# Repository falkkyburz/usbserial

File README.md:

# USB to Serial Converter

This is a USB to serial (UART) converter employing the FTDI FT230XS chip designed in KiCad. I 
included an optional digital isolator for noisy environments or when galvanic 
isolation is required. 

## BOM

I also included the interactive html BOM (usbserial.html) 

| References     | Value                     | Footprint | Quantity |
|----------------|---------------------------|-----------|----------|
| C1, C2, C7, C8 | 100n                      | 0603      | 4        |
| C4, C5         | 47p                       | 0603      | 2        |
| C3             | 10n                       | 0603      | 1        |
| C6             | 4.7u                      | 0603      | 1        |
| R1, R2         | 270R                      | 0603      | 2        |
| R3, R4         | 27R                       | 0603      | 2        |
| D1, D2         | green                     | 0603      | 2        |
| U1             | Si8642BB-B-IS1            | SOIC-16   | 1        |
| U2             | FT230XS                   | SSOP-16   | 1        |
| FB1            | MI0603J601R-10            | 0603      | 1        |
| JP1 - JP6      | Jumper (if U1 not placed) | 1206      | 6        |
| J1             | Header 4pin, 2.54mm       | -         | 1        |
| J2             | USB-Micro WE 629105150521 | -         | 1        |

## Datasheets

* [Si8642BB-B-IS1](https://www.silabs.com/documents/public/data-sheets/si864x-datasheet.pdf)
* [FT230XS](https://www.ftdichip.com/Support/Documents/DataSheets/ICs/DS_FT230X.pdf)
* [MI0603J601R-10](https://www.laird.com/sites/default/files/2019-04/MI0603J601R-10_0.pdf)
* [WE 629105150521](https://www.we-online.com/catalog/en/COM_MICRO_SMT_TYPE_B_HORIZONTAL_HIGH_CURRENT/)

## Prototype

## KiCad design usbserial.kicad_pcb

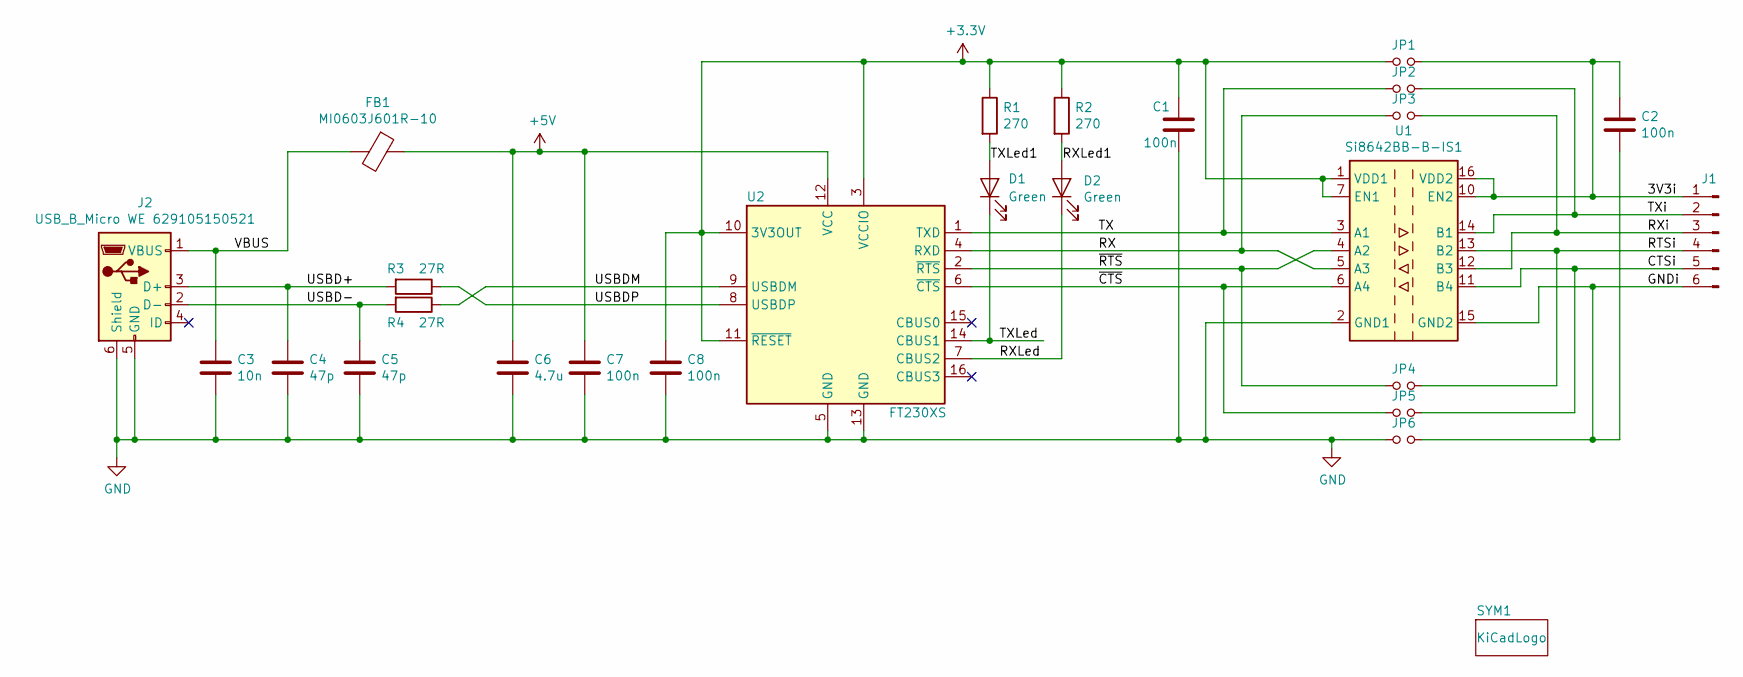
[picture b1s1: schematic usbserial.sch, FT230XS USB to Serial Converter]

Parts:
C1, C2, C7, C8: 100n; C_0603_1608Metric_Pad1.05x0.95mm_HandSolder
C3: 10n; C_0603_1608Metric_Pad1.05x0.95mm_HandSolder
C4, C5: 47p; C_0603_1608Metric_Pad1.05x0.95mm_HandSolder
C6: 4.7u; C_0603_1608Metric_Pad1.05x0.95mm_HandSolder
D1, D2: Green; LED_0603_1608Metric_Pad1.05x0.95mm_HandSolder
FB1: MI0603J601R-10; L_0603_1608Metric_Pad1.05x0.95mm_HandSolder
J1: Conn_01x06_Male; PinHeader_1x06_P2.54mm_Vertical
J2: USB_B_Micro WE 629105150521; USB_Micro-B_Wuerth_629105150521_CircularHoles
JP1, JP2, JP3, JP4, JP5, JP6: Jumper_NO_Small; R_1206_3216Metric_Pad1.42x1.75mm_HandSolder
R1, R2: 270; R_0603_1608Metric_Pad1.05x0.95mm_HandSolder
R3, R4: 27R; R_0603_1608Metric_Pad1.05x0.95mm_HandSolder
SYM1: KiCadLogo; KiCad-Logo2_5mm_SilkScreen
U1: Si8642BB-B-IS1; SOIC-16_3.9x9.9mm_P1.27mm
U2: FT230XS; SSOP-16_3.9x4.9mm_P0.635mm

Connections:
+3V3: C1.1, C8.1, JP1.1, R1.1, R2.1, U1.1 (VDD1), U1.7 (EN1), U2.3 (VCCIO), U2.10 (3V3OUT), U2.11 (~RESET)
+5V: C6.1, C7.1, FB1.1, U2.12 (VCC)
/3V3i: C2.1, J1.1, JP1.2, U1.10 (EN2), U1.16 (VDD2)
/CTSi: J1.5, JP5.2, U1.11 (B4)
/GNDi: C2.2, J1.6, JP6.2, U1.9 (GND2), U1.15 (GND2)
/RTSi: J1.4, JP4.2, U1.13 (B2)
/RX: JP3.1, U1.5 (A3), U2.4 (RXD)
/RXLed: D2.1 (K), U2.7 (CBUS2)
/RXLed1: D2.2 (A), R2.2
/RXi: J1.3, JP3.2, U1.12 (B3)
/TX: JP2.1, U1.3 (A1), U2.1 (TXD)
/TXLed: D1.1 (K), U2.14 (CBUS1)
/TXLed1: D1.2 (A), R1.2
/TXi: J1.2, JP2.2, U1.14 (B1)
/USBD+: C4.1, J2.3 (D+), R3.2
/USBD-: C5.1, J2.2 (D-), R4.2
/USBDM: R4.1, U2.9 (USBDM)
/USBDP: R3.1, U2.8 (USBDP)
/VBUS: C3.1, FB1.2, J2.1 (VBUS)
/~CTS~: JP5.1, U1.6 (A4), U2.6 (~CTS)
/~RTS~: JP4.1, U1.4 (A2), U2.2 (~RTS)
GND: C1.2, C3.2, C4.2, C5.2, C6.2, C7.2, C8.2, J2.5 (GND), J2.6 (Shield), JP6.1, U1.2 (GND1), U1.8 (GND1), U2.5 (GND), U2.13 (GND)

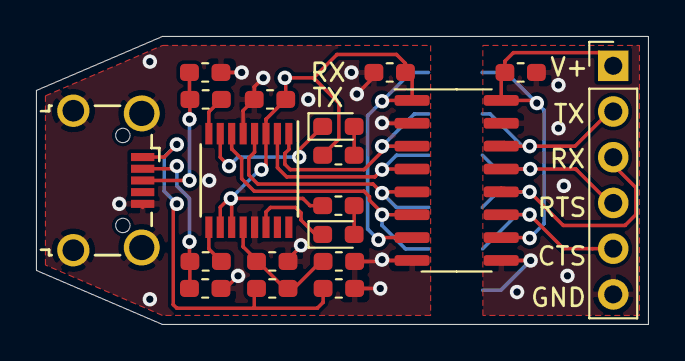
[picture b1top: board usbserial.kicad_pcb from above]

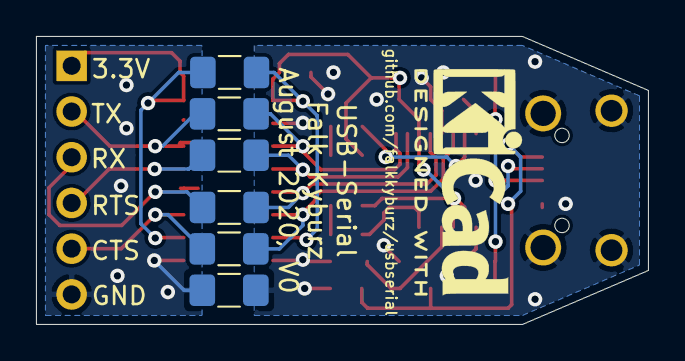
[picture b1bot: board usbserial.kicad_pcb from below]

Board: 2 copper layers, 34.0 x 16.0 mm, 26 parts (7 on the bottom side), 22 nets.

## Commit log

2020-08-28 Added usbserial.html, usbserial.png and README.md
2020-09-13 Added prototype picture usbserial_prototype.jpg.
